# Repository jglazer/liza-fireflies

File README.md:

# Liza Fireflies

An art project for Liza Stark's wedding celebration.

Read all about it in [this blog post](http://johnkeefe.net/making-lizas-fireflies).

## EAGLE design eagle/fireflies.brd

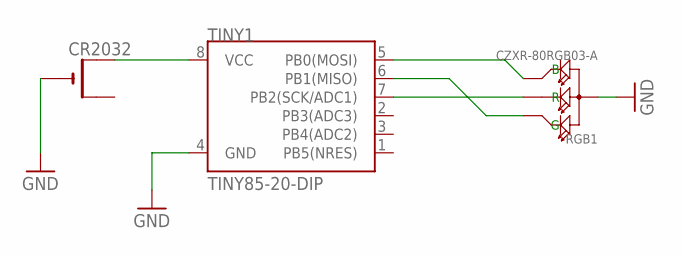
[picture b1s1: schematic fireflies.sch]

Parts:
CR2032: CR2032SMT; CR2032-SMD
RGB1: CZXR-80RGB03-A; LED4-2.0-D8.0MM
TINY1: TINY85-20-DIP; DIP08

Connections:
GND: CR2032.-, RGB1.2 (+), TINY1.4 (GND)
unnamed: RGB1.4 (B), TINY1.5 (PB0(MOSI))
unnamed: RGB1.1 (R), TINY1.7 (PB2(SCK/ADC1))
unnamed: RGB1.3 (G), TINY1.6 (PB1(MISO))
unnamed: CR2032.+$1 (+), TINY1.8 (VCC)

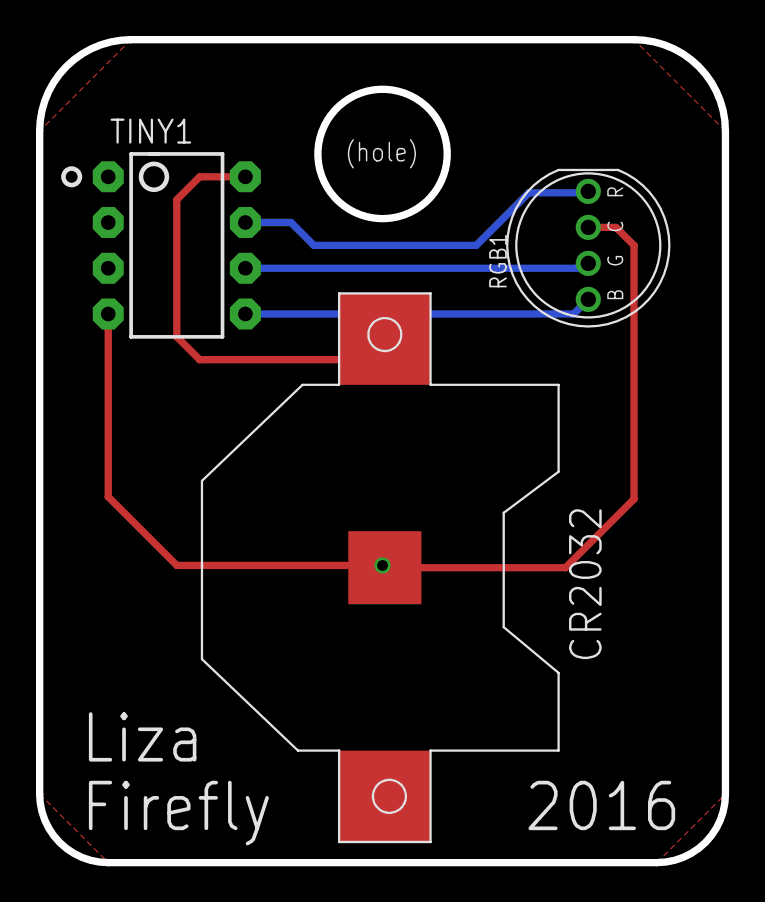
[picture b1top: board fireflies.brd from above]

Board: 2 copper layers, 38.1 x 45.7 mm, 3 parts (0 on the bottom side), 5 nets.

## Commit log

2016-07-29 added eagle files
2016-09-27 added attiny code
2016-09-27 renamed code folder to attiny

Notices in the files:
parts and their libraries:
SparkFun-DigitalIC: Licensing: Creative Commons ShareAlike 4.0 International - https://creativecommons.org/licenses/by-sa/4.0
